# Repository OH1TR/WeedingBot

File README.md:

# This is collection of bits and pieces to build weeding bot. (or something)

Bot is build on frame of old lawn mover. Jetson Nano board handles communication with windows client. There is ZED-camera on board for images. Some custom PCB:s and China boards to contol motors.

Code is a mess, but it moves.. :-)

Video: https://www.facebook.com/100010379521880/videos/999905427032099/

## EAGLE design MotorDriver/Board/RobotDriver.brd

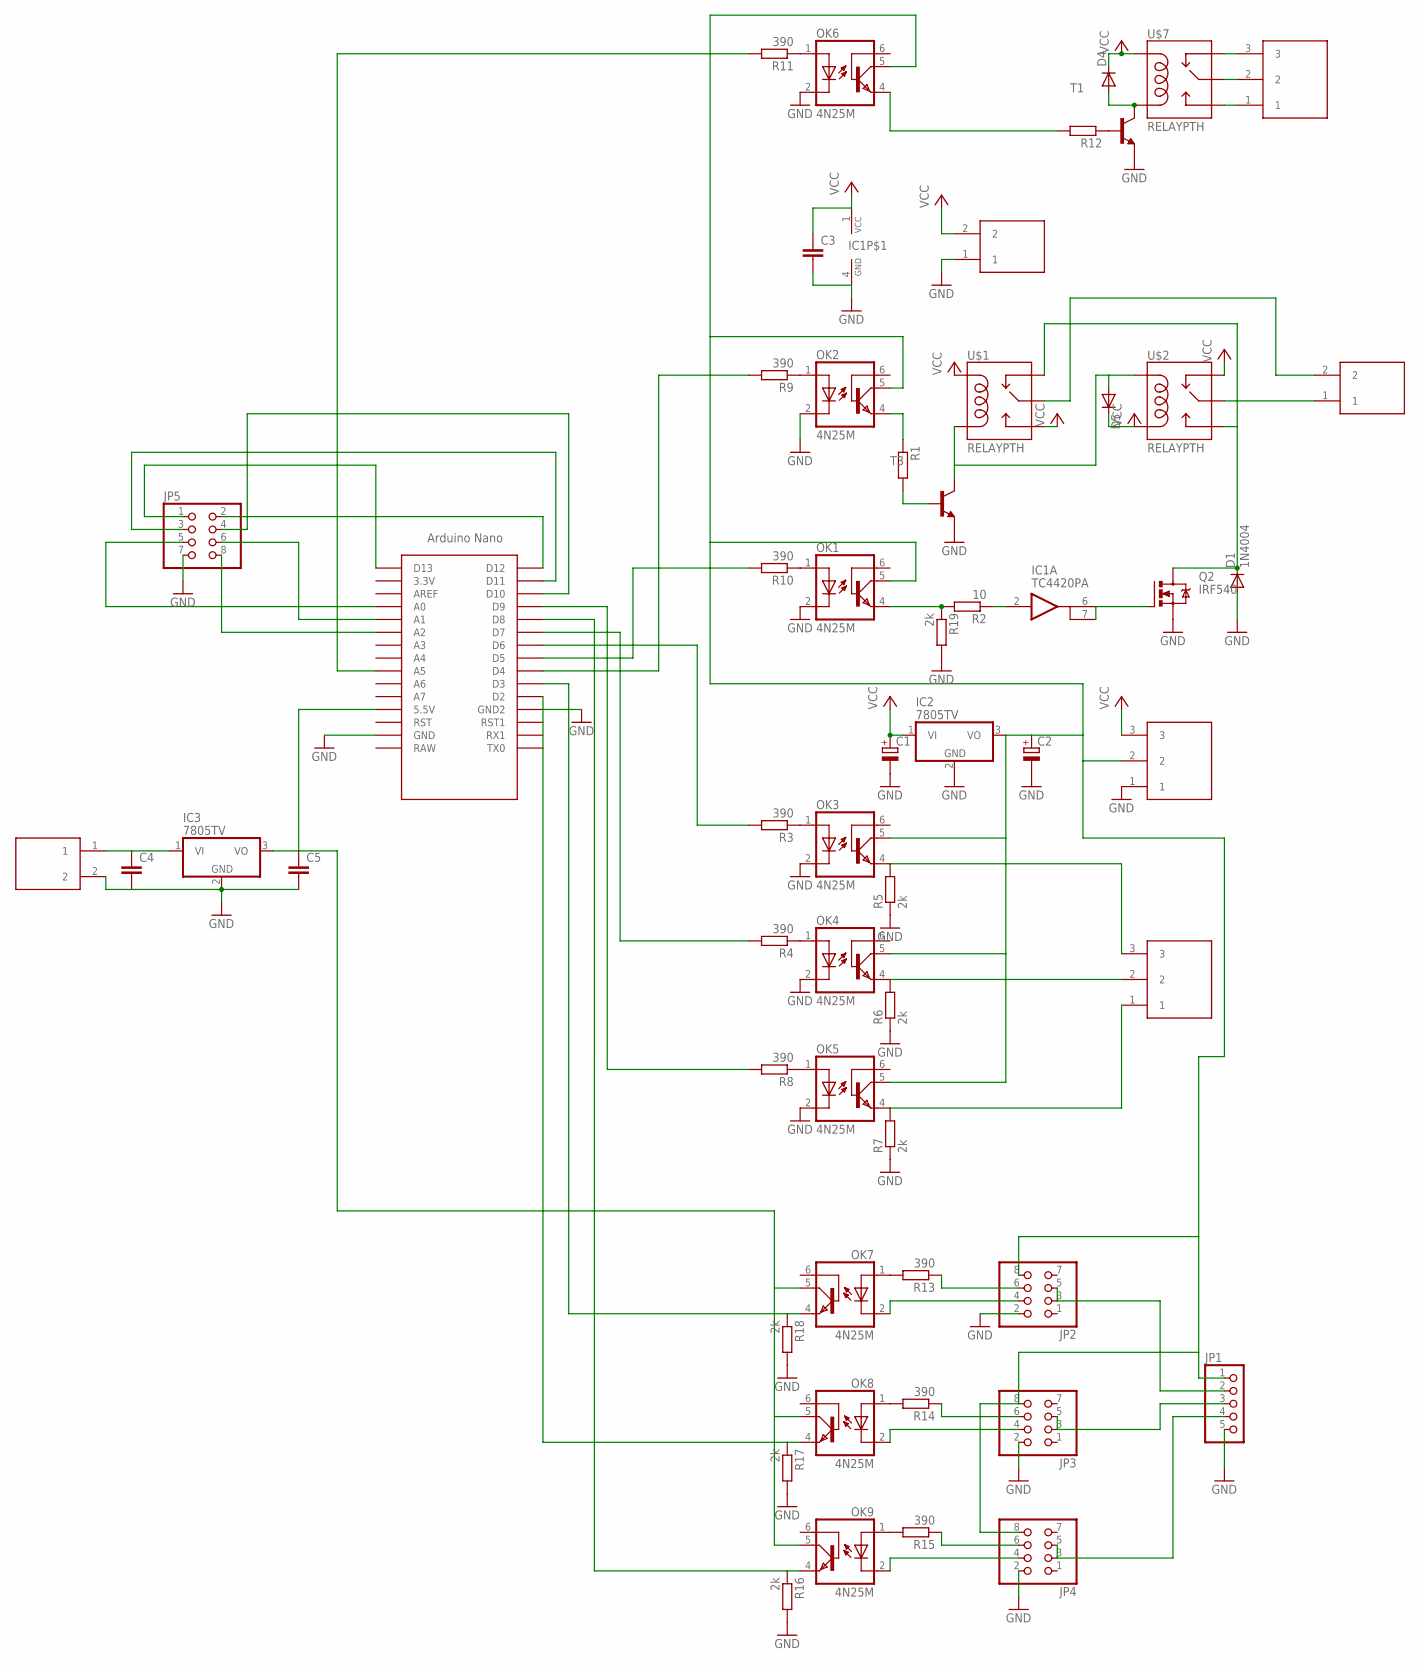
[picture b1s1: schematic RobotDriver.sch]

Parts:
C1, C2: CPOL-EUE5-10.5; E5-10,5
C3, C4, C5: C-EUC1206; C1206
D1: 1N4004; DO41-10
D4, D5: DIODE-DO214AA; DO214AA
IC1: TC4420PA; DIP08
IC2, IC3: 7805TV; TO220V
JP1: PINHD-1X5; 1X05
JP2, JP3, JP4, JP5: PINHD-2X4; 2X04
OK1, OK2, OK3, OK4, OK5, OK6, OK7, OK8, OK9: 4N25M; DIL06
Q2: IRF540; TO220BV
R1, R12: R-EU_R1210; R1210
R2: 10; R1210
R3, R4, R8, R9, R10, R11, R13, R14, R15: 390; R1210
R5, R6, R7, R16, R17, R18, R19: 2k; R1210
T1, T3: BC817-16-NPN-SOT23-BEC; SOT23-BEC
U$1, U$2, U$7: RELAYPTH; SRD-05VDC-SL-C
U$3: NANO
U$4, U$5, U$10: 2EDG-2; 2EGD-2-PAK
U$6, U$8, U$9: 2EDG-3; 2EGD-3-PAK

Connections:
GND: C1.-, C2.-, C3.2, C4.2, C5.2, D1.A, IC1.4 (GND), IC1.5 (GND), IC2.2 (GND), IC3.2 (GND), JP1.5, JP2.2, JP3.2, JP4.2, JP5.7, OK1.2 (C), OK2.2 (C), OK3.2 (C), OK4.2 (C), OK5.2 (C), OK6.2 (C), Q2.S, R5.1, R6.1, R7.1, R16.2, R17.2, R18.2, R19.2, T1.E, T3.E, U$3.GND, U$3.GND1 (GND2), U$5.1, U$9.1, U$10.2
unnamed: R1.2, T3.B
unnamed: D5.A, T3.C, U$1.COIL0, U$2.COIL1
unnamed: OK2.4 (EMI), R1.1
unnamed: D1.C, Q2.D, U$1.SWCLOSED (SWCLOSE), U$2.SWOPEN
unnamed: OK1.4 (EMI), R2.2, R19.1
unnamed: OK3.1 (A), R3.1
unnamed: OK2.1 (A), R9.1
unnamed: OK1.1 (A), R10.1
unnamed: R9.2, U$3.D4
unnamed: U$2.SWCOMMON, U$4.1
unnamed: U$1.SWCOMMON, U$4.2
unnamed: IC1.6 (OUT1), IC1.7 (OUT2), Q2.G
unnamed: C2.+, IC2.3 (VO), JP1.1, JP2.8, JP3.8, JP4.8, OK1.5 (COL), OK2.5 (COL), OK3.5 (COL), OK4.5 (COL), OK5.5 (COL), OK6.5 (COL), U$9.2
unnamed: OK3.4 (EMI), R5.2, U$6.3
unnamed: OK4.4 (EMI), R6.2, U$6.2
unnamed: OK5.4 (EMI), R7.2, U$6.1
unnamed: OK4.1 (A), R4.1
unnamed: OK5.1 (A), R8.1
unnamed: OK6.1 (A), R11.1
unnamed: D4.A, T1.C, U$7.COIL0
unnamed: R12.1, T1.B
unnamed: JP2.4, OK7.2 (C)
unnamed: OK6.4 (EMI), R12.2
unnamed: JP3.6, R14.1
unnamed: OK7.1 (A), R13.2
unnamed: OK8.1 (A), R14.2
unnamed: OK9.1 (A), R15.2
unnamed: JP3.4, OK8.2 (C)
unnamed: JP2.6, R13.1
unnamed: JP4.6, R15.1
unnamed: JP4.4, OK9.2 (C)
unnamed: IC1.2 (IN), R2.1
unnamed: C5.1, IC3.3 (VO), OK7.5 (COL), OK8.5 (COL), OK9.5 (COL), U$3.5V (5.5V)
unnamed: JP5.2, U$3.D12
unnamed: JP1.2, JP2.3, JP2.5
unnamed: JP1.3, JP3.3, JP3.5
unnamed: JP1.4, JP4.3, JP4.5
unnamed: OK9.4 (EMI), R16.1, U$3.D8
unnamed: OK8.4 (EMI), R17.1, U$3.D2
unnamed: OK7.4 (EMI), R18.1, U$3.D3
unnamed: U$7.SWCLOSED (SWCLOSE), U$8.3
unnamed: U$7.SWCOMMON, U$8.2
unnamed: U$7.SWOPEN, U$8.1
unnamed: C4.1, IC3.1 (VI), U$10.1
unnamed: R11.2, U$3.A5
unnamed: JP5.1, U$3.D13
unnamed: R10.2, U$3.D5
unnamed: R3.2, U$3.D6
unnamed: R4.2, U$3.D7
unnamed: R8.2, U$3.D9
unnamed: JP5.3, U$3.D11
unnamed: JP5.4, U$3.D10
unnamed: JP5.5, U$3.A0
unnamed: JP5.6, U$3.A1
unnamed: JP5.8, U$3.A2
VCC: C1.+, C3.1, D4.C, D5.C, IC1.1 (VCC), IC1.8 (VCC), IC2.1 (VI), U$1.COIL1, U$1.SWOPEN, U$2.COIL0, U$2.SWCLOSED (SWCLOSE), U$5.2, U$7.COIL1, U$9.3

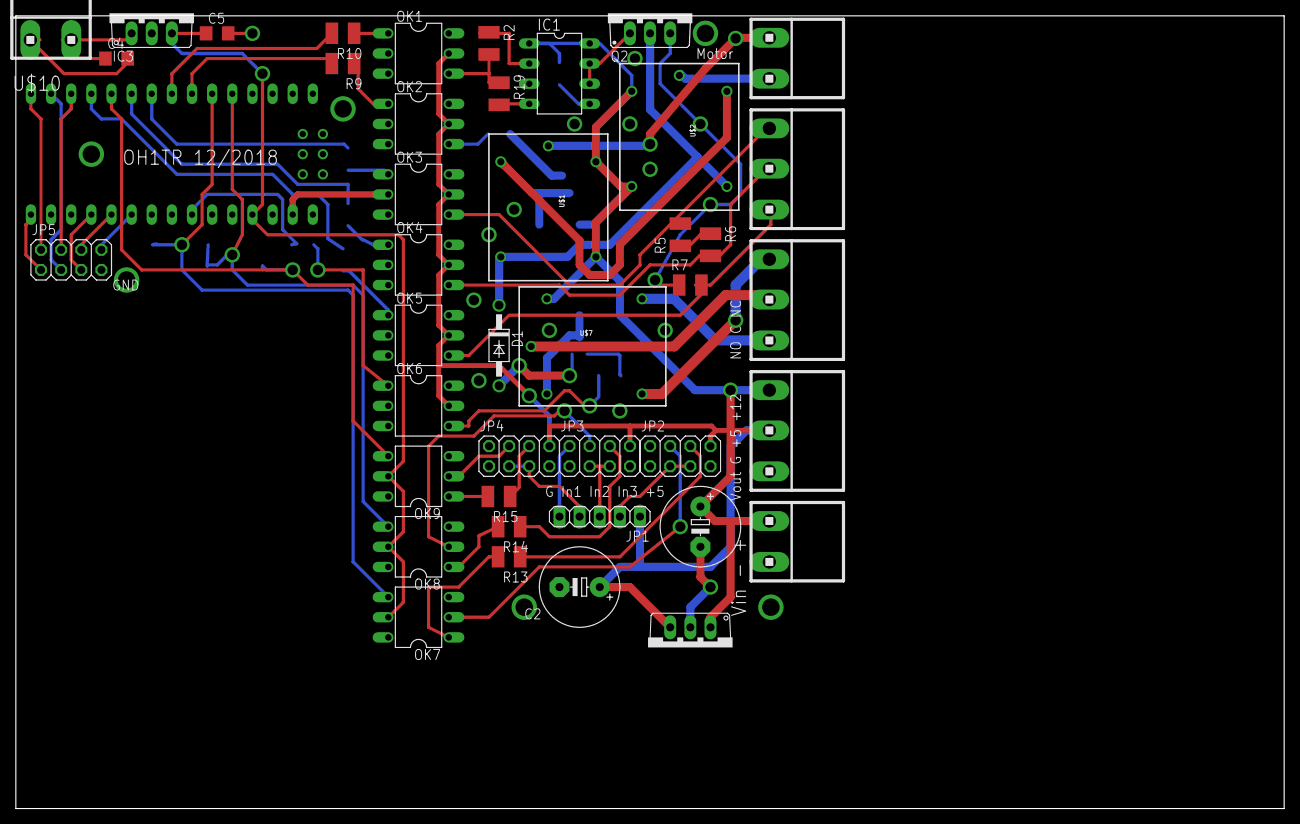
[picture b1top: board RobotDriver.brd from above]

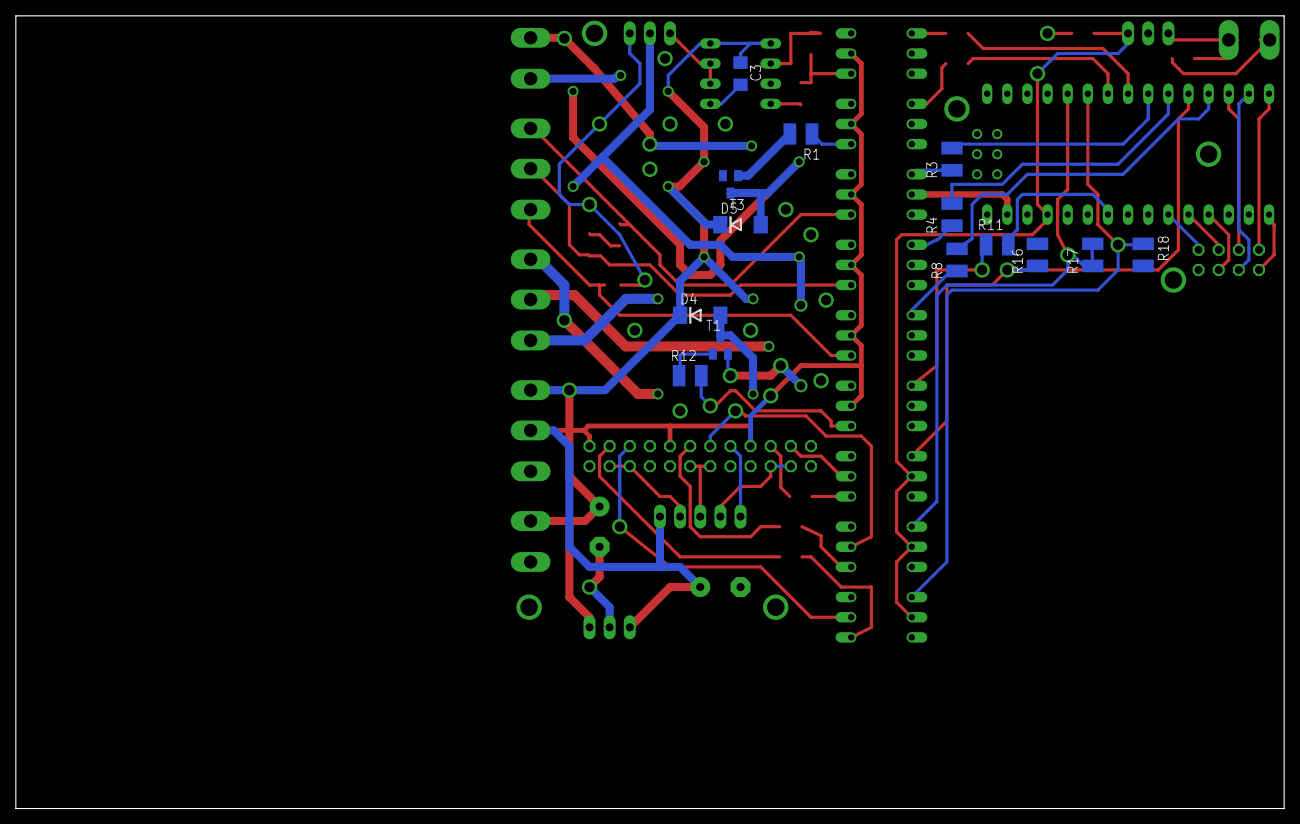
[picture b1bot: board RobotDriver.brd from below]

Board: 2 copper layers, 160.0 x 100.0 mm, 57 parts (14 on the bottom side), 57 nets.

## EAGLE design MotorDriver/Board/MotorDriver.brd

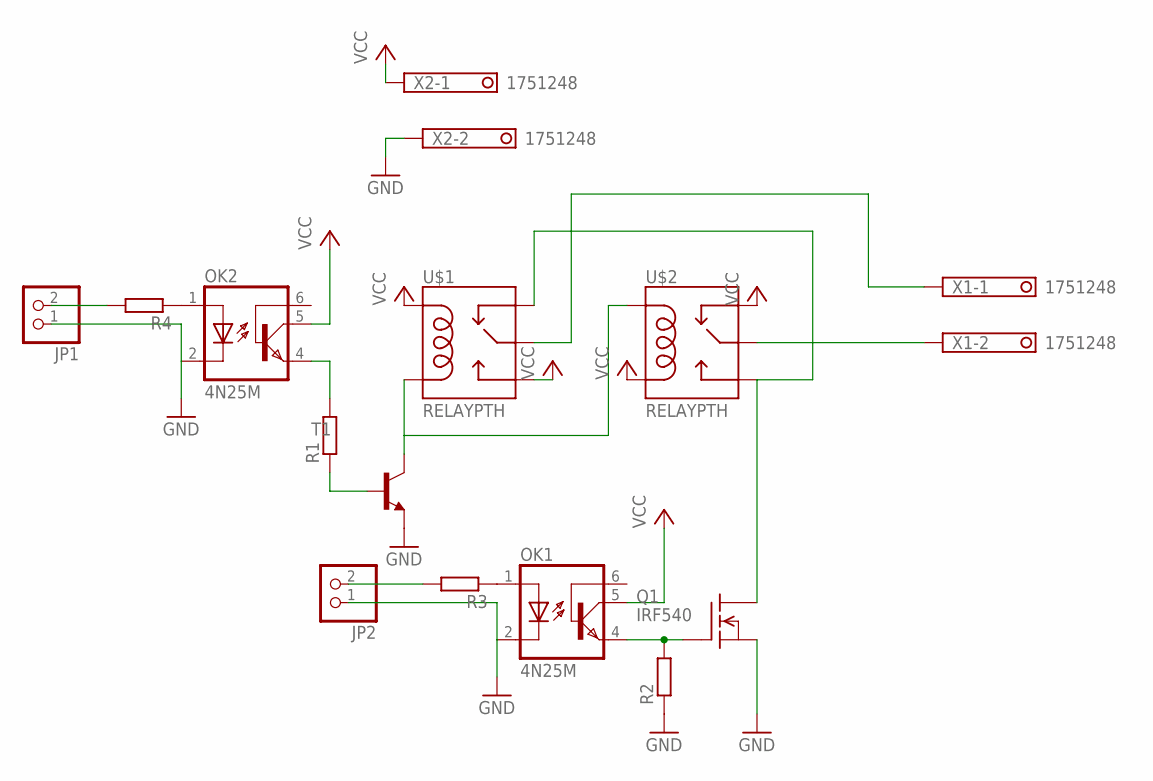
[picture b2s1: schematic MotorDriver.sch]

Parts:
JP1, JP2: PINHD-1X2; 1X02
OK1, OK2: 4N25M; DIL06
Q1: IRF540; TO220
R1, R2, R3, R4: R-EU_0204/7; 0204/7
T1: 2N2222-NPN-TO92-EBC; TO92-EBC
U$1, U$2: RELAYPTH; SRD-05VDC-SL-C
X1, X2: 1751248

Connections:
GND: JP1.1, JP2.1, OK1.2 (C), OK2.2 (C), Q1.3 (S), R2.1, T1.E, X2.2
unnamed: R1.1, T1.B
unnamed: T1.C, U$1.COIL0, U$2.COIL1
unnamed: OK2.4 (EMI), R1.2
unnamed: Q1.2 (D), U$1.SWCLOSED (SWCLOSE), U$2.SWOPEN
unnamed: OK1.4 (EMI), Q1.1 (G), R2.2
unnamed: OK1.1 (A), R3.1
unnamed: OK2.1 (A), R4.1
unnamed: JP1.2, R4.2
unnamed: JP2.2, R3.2
unnamed: U$2.SWCOMMON, X1.2
unnamed: U$1.SWCOMMON, X1.1
VCC: OK1.5 (COL), OK2.5 (COL), U$1.COIL1, U$1.SWOPEN, U$2.COIL0, U$2.SWCLOSED (SWCLOSE), X2.1

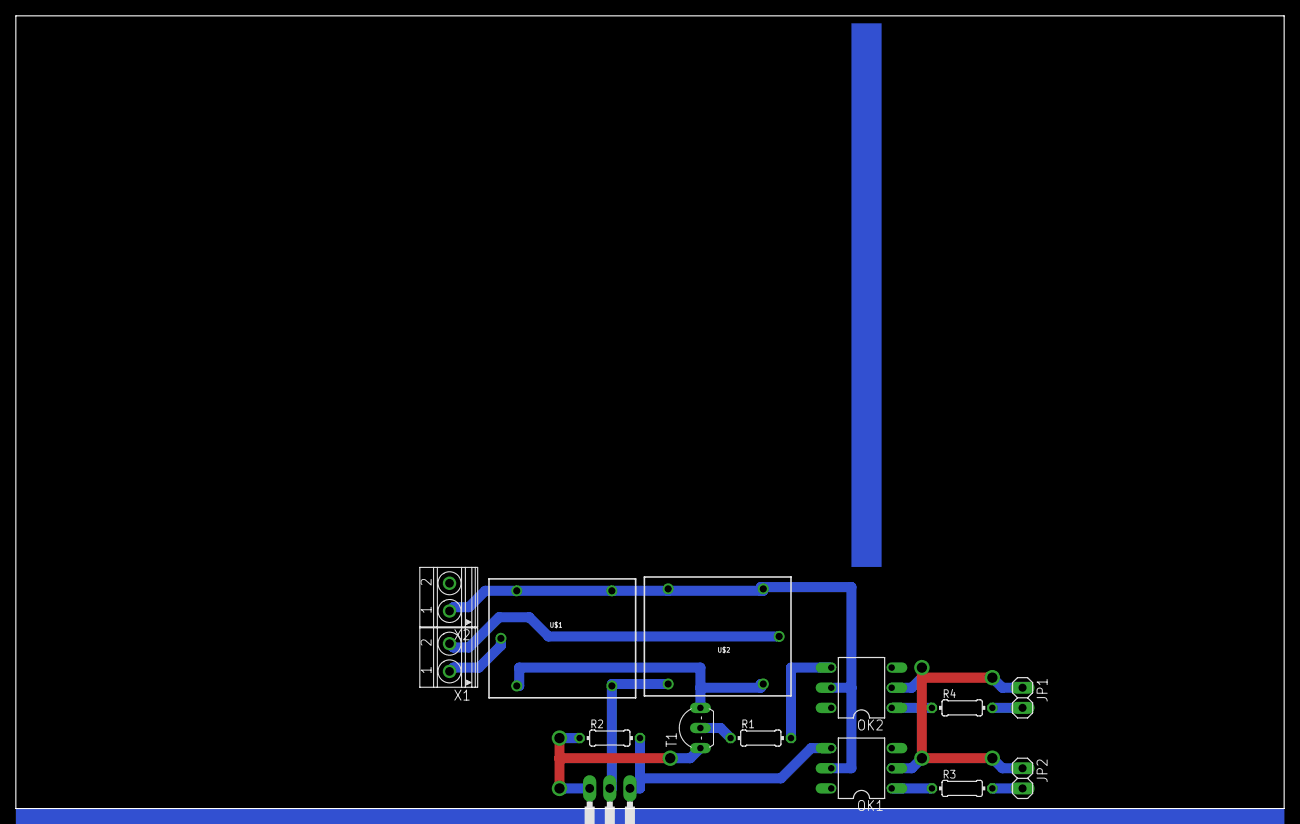
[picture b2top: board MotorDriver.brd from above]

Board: 2 copper layers, 160.0 x 100.0 mm, 14 parts (0 on the bottom side), 13 nets.

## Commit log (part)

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2017-12-09 Initial commit.
2017-12-10 First moves...:-)
2018-03-04 Added image editting tool.(that cannot edit anything yet)
2018-03-07 Stuff...
2020-01-26 Code for controlling robot remotely.
2020-01-26 Test run done!
2020-01-26 Fixed readme
2022-02-11 Bump Google.Protobuf from 3.11.2 to 3.15.0 in /RobotDriver/RobotClient
    Bumps [Google.Protobuf](https://github.com/protocolbuffers/protobuf) from 3.11.2 to 3.15.0.
    - [Release notes](https://github.com/protocolbuffers/protobuf/releases)
    - [Changelog](https://github.com/protocolbuffers/protobuf/blob/master/generate_changelog.py)
    - [Commits](https://github.com/protocolbuffers/protobuf/compare/v3.11.2...v3.15.0)
    ---
    updated-dependencies:
2026-06-05 Update MotorDriver.ino
    wasd drive.
2026-06-06 Update MotorDriver.ino
    .
2026-06-06 BotControl
